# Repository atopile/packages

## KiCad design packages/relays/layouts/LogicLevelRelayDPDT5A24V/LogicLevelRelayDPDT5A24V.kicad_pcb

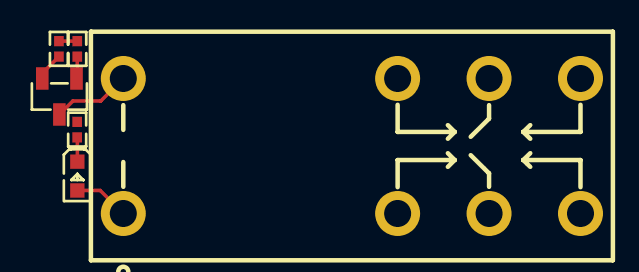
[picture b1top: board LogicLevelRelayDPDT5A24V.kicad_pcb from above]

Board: 2 copper layers, 6 parts (0 on the bottom side), 6 nets.

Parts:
K1: RELAY-TH_G2R-2
LED1: LED0603-RD
Q1: SOT-23-3_L2.9-W1.3-P1.90-LS2.4-BR
R1, R2: 10000Ω; R0402
R3: 47000Ω; R0402

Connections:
anode: K1.1, LED1.2
cathode: LED1.1, R3.1
contacts[1]: K1.8, Q1.3
gate: Q1.1, R2.2
line: R1.1, R2.1
lv: Q1.2, R1.2, R3.2
